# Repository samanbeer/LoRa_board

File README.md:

# LoRa Board

[Forge Project](https://forge.hackclub.com/projects/3508)

---

## Project Overview

- **What is it?** A small,  custom LoRa board with **ESP32-S3-WROOM-1** and with the **SX1262** chip which is radio transceiver.
- **What does it do?** It can be used for wireless data communication with extremely big range. 
- ****Why does it exist?** Most of LoRa development boards are extremly pricey or use older transceivers or dont have USB-C. 

---

## Why I Made This

i saw a video about it. And saw how cool it is and I wanted to build custom meshtastic node and try the P2P comunication on it. 

## Project Gallery

### 3D PCB Renders

### 3D Board Views

### PCB Layout & Schematic

### 3D Enclosure (Fusion 360)

*3D printable case is made in Fusion 360. All CAD and 3D model files are in the [`CAD/`](CAD/) folder.*

---

## Assembly Guide

### Required Tools & Materials

- Soldering iron
- Solder wire and flux
- Tweezers for placing small SMD components
- 3D Printer (for printing the custom case)

### Assembly Steps

1. **Starts with small schips :**
   - **SX1262** - align carefully, use soldering iron with sharp tip with flux).
   - **PE42359** and **AP2112K-3.3** - soldern one pin, verify if its alligned, and solder remaining pins.
2. **Small passive components:**
   - Solder small resistors and capacitors.
   - Solder inductors and the 32 MHz crystal.
3. **Connectors and Buttons:**
   - **USB-C connector** - Solder the THT tabs first for strength and then solder the pins using flux.
   - **U.FL connector** - Center and solder the RF signal pin and ground tabs.
   - Solder the **BOOT1** and **RESET1** buttons.
4. **ESP32-S3 Module:**
   - Place the **ESP32-S3-WROOM-1** module on its footprint pads.
   - Solder one pad, check alignment and then solder each pin.
5. **Enclosure and antenna :**
   - Plug the flexible flat antenna cable into the U.FL connector.
   - Slide the assembled PCB into case and snap the lid.
   - Stick the flat antenna on the top of the case or where you want it.

---

## BOM

| Reference                     | amount | Value / Component                       | Footprint / Package     | Link                                                                                                                                          | Cost (USD, incl. VAT) |
| ----------------------------- |:------:|:--------------------------------------- |:----------------------- |:--------------------------------------------------------------------------------------------------------------------------------------------- |:---------------------:|
| **BOOT1, RESET1**             | 2      | Tactile Switch (C&K RS-282G05A3-SM RT)  | SMD Button (6.0x3.5mm)  | [Mouser Link](https://cz.mouser.com/c/?q=RS-282G05A3-SM-RT)                                                                                   | $1.92                 |
| **C1, C4, C5, C10, C13, C18** | 6      | 100nF 50V X7R (GCM188R71H104KA57J)      | 0603 SMD                | [Mouser Link](https://cz.mouser.com/c/?q=GCM188R71H104KA57J)                                                                                  | $1.44                 |
| **C2, C12**                   | 2      | 10µF 10V X5R (C1608X5R1A106K080AC)      | 0603 SMD                | [Mouser Link](https://cz.mouser.com/c/?q=C1608X5R1A106K080AC)                                                                                 | $1.10                 |
| **C3**                        | 1      | 470nF 16V X7R (CL10B474KO8NNNC)         | 0603 SMD                | [Mouser Link](https://cz.mouser.com/c/?q=CL10B474KO8NNNC)                                                                                     | $0.13                 |
| **C6**                        | 1      | 8.2pF 50V C0G (CC0603DRNPO9BN8R2)       | 0603 SMD                | [Mouser Link](https://cz.mouser.com/en/ProductDetail/YAGEO/CC0603DRNPO9BN8R2?qs=AgBp2OyFlx9gbUJidsAGNA%3D%3D)                                 | $0.12                 |
| **C7**                        | 1      | 5.6pF 50V C0G (CC0603DRNPO9BN5R6)       | 0603 SMD                | [Mouser Link](https://cz.mouser.com/c/?q=CC0603DRNPO9BN5R6)                                                                                   | $0.12                 |
| **C8, C9**                    | 2      | 4.7µF 16V X5R (C1608X5R1C475K080AC)     | 0603 SMD                | [Mouser Link](https://cz.mouser.com/c/?q=C1608X5R1C475K080AC)                                                                                 | $0.60                 |
| **C11**                       | 1      | 1µF 16V X7R (C0603C105K4RAC)            | 0603 SMD                | [Mouser Link](https://cz.mouser.com/c/?q=C0603C105K4RAC)                                                                                      | $0.17                 |
| **C14, C15**                  | 2      | 47pF 50V C0G (CC0603JPNPO9BN470)        | 0603 SMD                | [Mouser Link](https://cz.mouser.com/en/ProductDetail/YAGEO/CC0603JPNPO9BN470?qs=AgBp2OyFlx%252BcxUrI4zA%252B5Q%3D%3D)                         | $0.24                 |
| **C16**                       | 1      | 1nF 50V X7R (CL10B102KB8NNNC)           | 0603 SMD                | [Mouser Link](https://cz.mouser.com/c/?q=CL10B102KB8NNNC)                                                                                     | $0.12                 |
| **C17**                       | 1      | 100pF 50V C0G (GRM1885C1H101JA01D)      | 0603 SMD                | [Mouser Link](https://cz.mouser.com/en/ProductDetail/Murata-Electronics/GRM1885C1H101JA01D?qs=H3lwsW1hsDt1I4guwPQ00A%3D%3D)                   | $0.13                 |
| **C19**                       | 1      | 1.8pF 50V C0G (CL10C1R8BB8NNNC)         | 0603 SMD                | [Mouser Link](https://cz.mouser.com/c/?q=CL10C1R8BB8NNNC)                                                                                     | $0.12                 |
| **C20**                       | 1      | 2.2pF 50V C0G (GRM1885C1H2R2BA01D)      | 0603 SMD                | [Mouser Link](https://cz.mouser.com/en/ProductDetail/Murata-Electronics/GRM1885C1H2R2BA01D?qs=9yYqngZLNofvaZZkO8y9FQ%3D%3D)                   | $0.17                 |
| **J1**                        | 1      | USB-C Receptacle 16P (DX07S016JA1R1500) | USB-C 16-Pin SMD+THT    | [Mouser Link](https://cz.mouser.com/c/?q=DX07S016JA1R1500)                                                                                    | $2.10                 |
| **J2**                        | 1      | U.FL Coaxial Connector (U.FL-R-SMT-1)   | U.FL SMD Vertical       | [Mouser Link](https://cz.mouser.com/c/?q=U.FL-R-SMT-1)                                                                                        | $1.85                 |
| **L1**                        | 1      | 15µH 150mA (LQM18DH150M70L)             | 0603 SMD                | [Mouser Link](https://cz.mouser.com/c/?q=LQM18DH150M70L)                                                                                      | $0.36                 |
| **L2**                        | 1      | 12nH High-Q RF (LQW18AN12NG00D)         | 0603 SMD                | [Mouser Link](https://cz.mouser.com/c/?q=LQW18AN12NG00D)                                                                                      | $0.16                 |
| **L3**                        | 1      | 47nH High-Q RF (LQW18AN47NG00D)         | 0603 SMD                | [Mouser Link](https://cz.mouser.com/c/?q=LQW18AN47NG00D)                                                                                      | $0.16                 |
| **L4**                        | 1      | 5.6nH High-Q RF (LQW18AN5N6C0ZD)        | 0603 SMD                | [Mouser Link](https://cz.mouser.com/c/?q=LQW18AN5N6C0ZD)                                                                                      | $0.18                 |
| **L5**                        | 1      | 6.8nH High-Q RF (LQW18AS6N8J0ZD)        | 0603 SMD                | [Mouser Link](https://cz.mouser.com/c/?q=LQW18AS6N8J0ZD)                                                                                      | $0.18                 |
| **R1, R2**                    | 2      | 5.1kΩ 1% (RC0603FR-135K1L)              | 0603 SMD                | [Mouser Link](https://cz.mouser.com/en/ProductDetail/YAGEO/RC0603FR-135K1L?qs=3EPPqRBBsNipUNdlRDI61Q%3D%3D)                                   | $0.24                 |
| **R3, R4**                    | 2      | 10kΩ 1% (RC0603FR-0710KL)               | 0603 SMD                | [Mouser Link](https://cz.mouser.com/en/ProductDetail/YAGEO/RC0603FR-0710KL?qs=grNVn54RoB%252B3GtjbJj3wJQ%3D%3D)                               | $0.24                 |
| **R5**                        | 2      | 100Ω 1% (RC0603FR-07100RL)              | 0603 SMD                | [Mouser Link](https://cz.mouser.com/c/?q=RC0603FR-07100RL)                                                                                    | $0.24                 |
| **TP1, TP2**                  | 1      | Pin Header 1x40 (Harwin M20-9994045)    | PinHeader 1x01 (2.54mm) | [Mouser Link](https://cz.mouser.com/c/?q=M20-9994045)                                                                                         | $2.31                 |
| **U1**                        | 1      | ESP32-S3-WROOM-1-N8 (8MB Flash)         | RF Module               | [Mouser Link](https://cz.mouser.com/en/ProductDetail/Espressif-Systems/ESP32-S3-WROOM-1-N8?qs=sGAEpiMZZMu3sxpa5v1qrpuLb1YRQvRH486xd1meH8w%3D) | $6.79                 |
| **U2**                        | 1      | SPDT RF Switch (PE42359SCAA-Z)          | SOT-363 (SC-70-6)       | [Mouser Link](https://cz.mouser.com/c/?q=PE42359SCAA-Z)                                                                                       | $1.18                 |
| **U3**                        | 1      | SX1262IMLTRT LoRa Transceiver           | QFN-24 (4x4mm)          | [Mouser Link](https://cz.mouser.com/c/?q=SX1262IMLTRT)                                                                                        | $10.83                |
| **U4**                        | 1      | AP2112K-3.3TRG1 LDO 3.3V 600mA          | SOT-23-5                | [Mouser Link](https://cz.mouser.com/c/?q=AP2112K-3.3TRG1)                                                                                     | $0.32                 |
| **Y1**                        | 1      | 32MHz Crystal (ABM8-32.000MHZ-10-B1U-T) | SMD 3225-4Pin           | [Mouser Link](https://cz.mouser.com/c/?q=ABM8-32.000MHZ-10-B1U-T)                                                                             | $0.59                 |
| **PCB**                       | 1      |                                         |                         | [JLCPCB](https://jlcpcb.com)                                                                                                                  | ~$10                  |
| **shipping Mouser**           |        |                                         |                         |                                                                                                                                               | $33.80                |
| **Mouser Order**              |        |                                         |                         | [cart.XLS file](file:///D:/!Documents/KiCad/LoRa_Board/Basket_Oct20_1158AM.xls)                                                               | **$67.91**            |
| **Total**                     |        | Cost of everything                      |                         |                                                                                                                                               | **$77.91**            |

## How to Use

1. **Antenna First:** make sure its a compatible 868 MHz antenna. Never turn the board ON if there is no antenna! 
2. **Power:** Plug a USB-C cable into the board. 
3. **Flashing Firmware & Meshtastic:**
   - Hold down the **BOOT1** button, press and release the **RESET1** button, then release **BOOT1** to enter bootloader mode.
   - Check out the [`Firmware/`](Firmware/) directory for the ready-to-use **Meshtastic** configuration (`variant.h`), pin mappings, and a complete [RadioLib](https://github.com/jgromes/RadioLib) test sketch for PlatformIO/Arduino!
4. **Wireless Communication:**
   - Configure to 868 MHz and try sending/receiving LoRa packets.
   - Perfect for Meshtastic mesh nodes, remote telemetry sensors, and off-grid communication!

---

- Designed by **Šámot** in [Hack Club Forge](https://forge.hackclub.com/projects/3508) project.

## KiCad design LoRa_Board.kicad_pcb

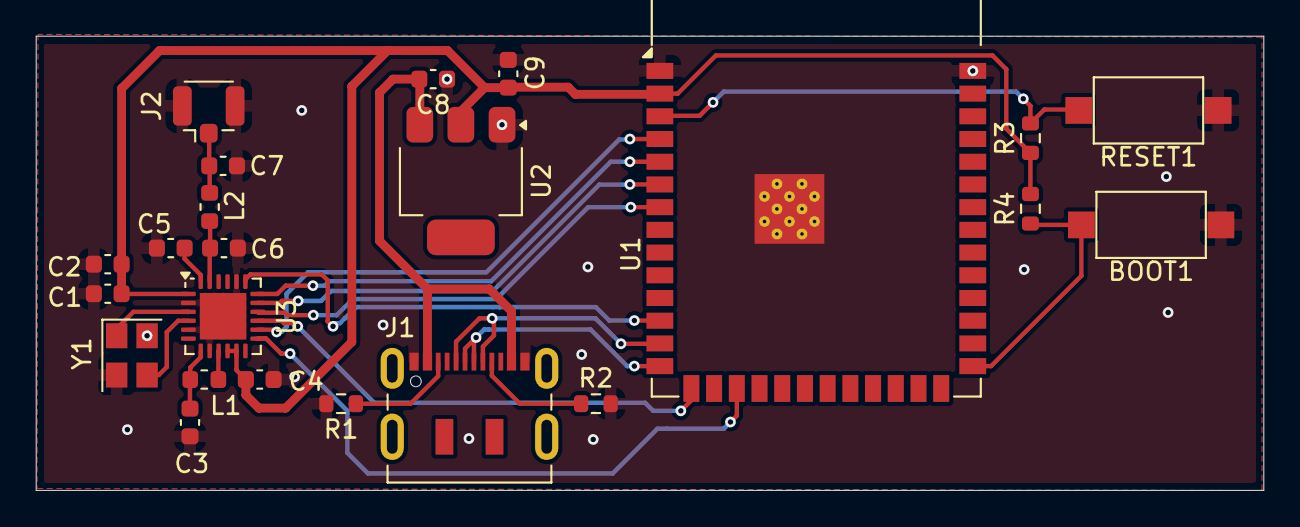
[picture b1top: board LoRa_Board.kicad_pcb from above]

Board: 2 copper layers, 68.7 x 25.4 mm, 23 parts (0 on the bottom side), 23 nets.

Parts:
BOOT1: SW_Push; SW_SPST_CK_RS282G05A3
C1, C3, C4, C5: 100nF; C_0603_1608Metric
C2, C8, C9: 10µF; C_0603_1608Metric
C6: 8.2pF; C_0603_1608Metric
C7: 5.6pF; C_0603_1608Metric
J1: USB_C_Receptacle_USB2.0_14P; USB_C_Receptacle_JAE_DX07S016JA1R1500
J2: Conn_Coaxial; U.FL_Hirose_U.FL-R-SMT-1_Vertical
L1: 15µH; L_0603_1608Metric
L2: 12nH; L_0603_1608Metric
R1, R2: R5.1k; R_0603_1608Metric
R3, R4: 10k; R_0603_1608Metric
RESET1: SW_Push; SW_SPST_CK_RS282G05A3
U1: ESP32-S3-WROOM-1
U2: AMS1117-3.3; SOT-223-3_TabPin2
U3: SX1262IMLTRT; QFN-24-1EP_4x4mm_P0.5mm_EP2.6x2.6mm
Y1: 32MHz; Crystal_SMD_3225-4Pin_3.2x2.5mm

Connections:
+3V3: C1.1, C2.2, C4.2, C9.1, R3.1, R4.2, U1.2 (3V3), U2.2 (VO), U3.1 (VDD_IN), U3.10 (VBAT), U3.11 (VBAT_IO)
+5V: C8.2, J1.A4 (VBUS), J1.A9 (VBUS), J1.B4 (VBUS), J1.B9 (VBUS), U2.3 (VI)
/BUSY: U1.4 (IO4), U3.14 (BUSY)
/DIO1: U1.17 (IO9), U3.13 (DIO1)
/MISO: U1.7 (IO7), U3.16 (MISO)
/MOSI: U1.6 (IO6), U3.17 (MOSI)
/NSS: U1.12 (IO8), U3.19 (NSS)
/RESET: U1.15 (IO3), U3.15 (~RESET)
/SCK: U1.5 (IO5), U3.18 (SCK)
/USB_D+: J1.A6 (D+), J1.B6 (D+), U1.14 (USB_D+)
/USB_D-: J1.A7 (D-), J1.B7 (D-), U1.13 (USB_D-)
GND: BOOT1.1, C1.2, C2.1, C3.1, C4.1, C5.2, C6.2, C7.2, C8.1, C9.2, J1.A1 (GND), J1.A12 (GND), J1.B1 (GND), J1.B12 (GND), J2.2 (Ext), R1.2, R2.2, RESET1.1, U1.1 (GND), U1.40 (GND), U1.41 (GND), U2.1 (GND), U3.2 (GND), U3.5 (GND), U3.8 (GND), U3.20 (GND), U3.25 (GND), Y1.2, Y1.4
unnamed: J1.A5 (CC1), R1.1
unnamed: J1.B5 (CC2), R2.1
unnamed: C7.1, J2.1 (In), L2.2
unnamed: R3.2, RESET1.2, U1.3 (EN)
unnamed: BOOT1.2, R4.1, U1.27 (IO0)
unnamed: L1.2, U3.9 (DCC_SW)
unnamed: C6.1, L2.1, U3.23 (RFO)
unnamed: C3.2, L1.1, U3.7 (VREG)
unnamed: C5.1, U3.24 (VR_PA)
unnamed: U3.3 (XTA), Y1.1
unnamed: U3.4 (XTB), Y1.3
